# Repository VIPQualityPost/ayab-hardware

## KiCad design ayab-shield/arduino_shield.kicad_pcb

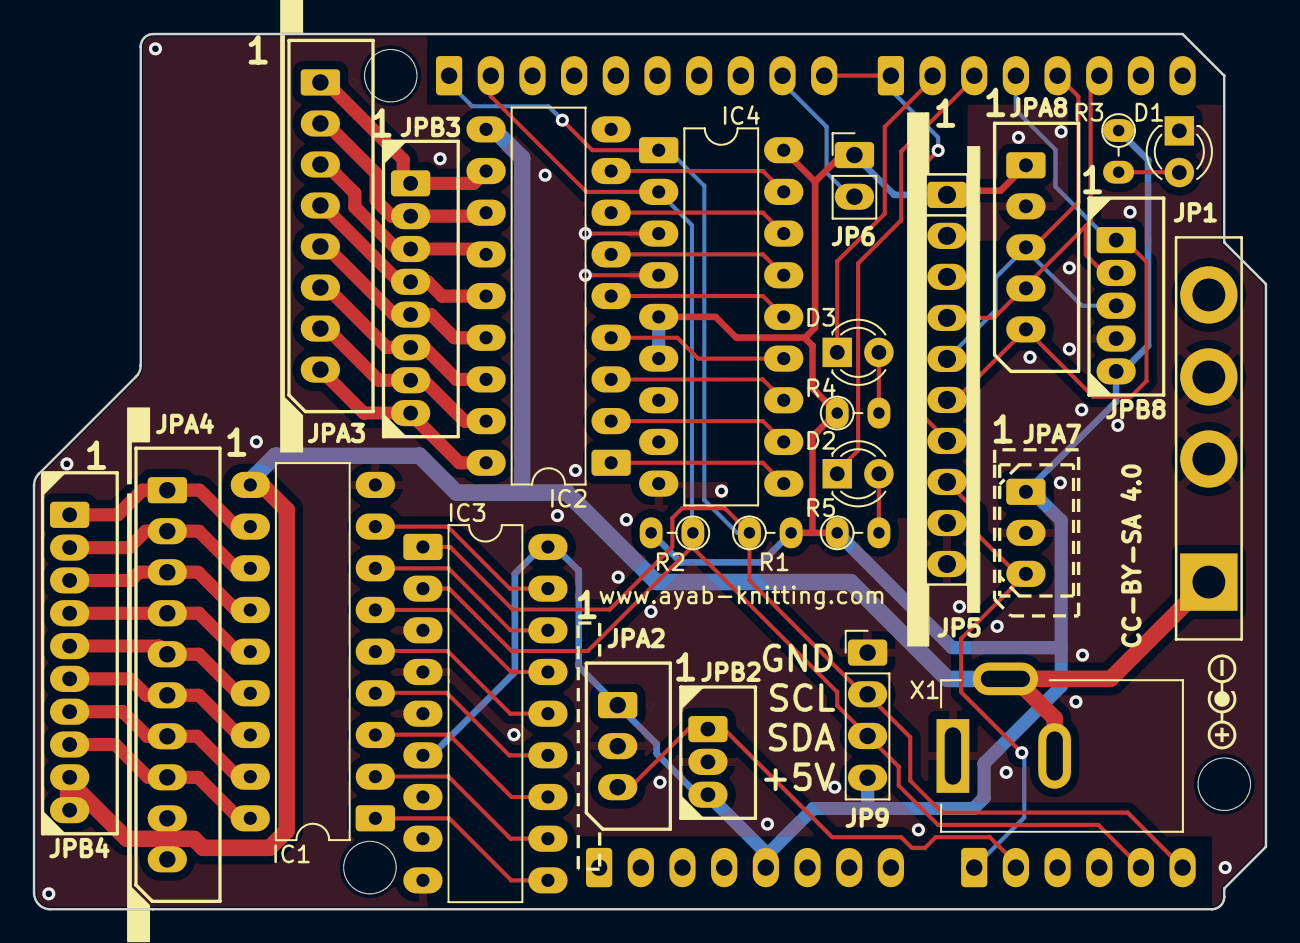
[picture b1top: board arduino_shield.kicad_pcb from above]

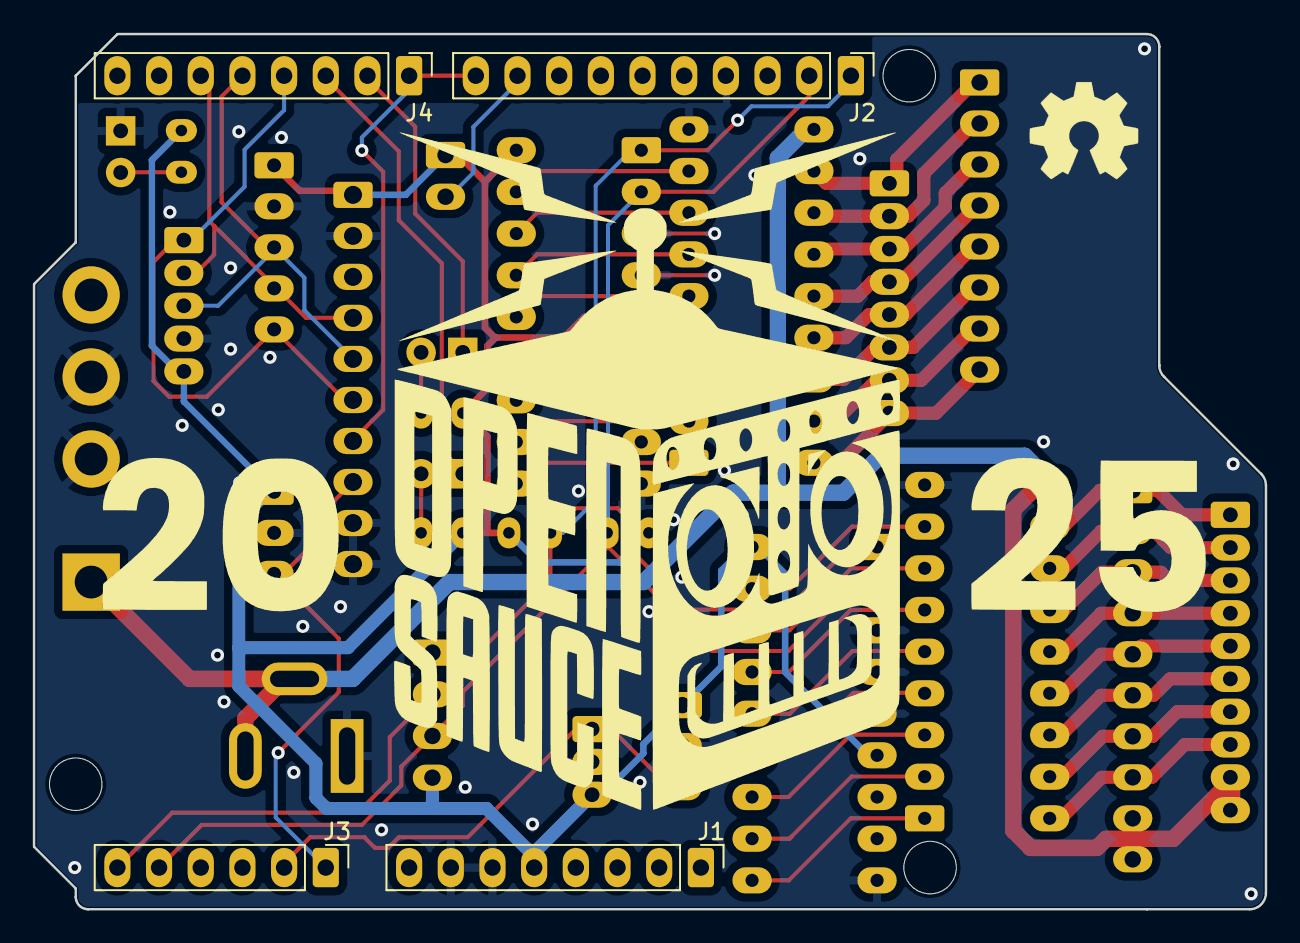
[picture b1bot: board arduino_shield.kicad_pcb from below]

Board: 2 copper layers, 75.1 x 53.3 mm, 34 parts (5 on the bottom side), 49 nets.

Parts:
D1: RED_3MM; LED_D3.0mm
D2: YEL_3MM; LED_D3.0mm
D3: GRN_3MM; LED_D3.0mm
IC1, IC2: ULN2803A; DIP-18_W7.62mm_LongPads
IC3, IC4: MCP2300X/P; DIP-18_W7.62mm_LongPads
J1: Power; PinHeader_1x08_P2.54mm_Vertical_LongPads
J2: Digital/PWM; PinHeader_1x10_P2.54mm_Vertical_LongPads
J3: Analog; PinHeader_1x06_P2.54mm_Vertical_LongPads
J4: Digital/PWM; PinHeader_1x08_P2.54mm_Vertical_LongPads
JP1: BROTHER POWER; Brother_4P
JP5: 1X10 2.5mm; HNC2-2.5P-10DS_LongPads
JP6: 1x2 2.5mm; PinHeader_1x02_P2.54mm_Vertical_LongPads
JP9: 1X5 2.5mm; PinHeader_1x04_P2.54mm_Vertical_LongPads
JPA2: 1X3 2.5mm; Molex_0022035035_or_Hirose_HNC2-2.5P-3DS_LongPads_dashed_bar
JPA3: 1X8 2.5mm; Molex_0022035085_or_Hirose_HNC2_2.5P_8DS_LongPads
JPA4: 1X10 2.5mm; Molex_0022035105_or_Hirose_HNC2-2.5P-10DS_LongPads
JPA7: 1X3 2.5mm; Molex_530140310_or_SPOX_5267-03A_1x03_P2.50mm_Vertical_Long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
JPA8: 1X5 2.5mm; Molex_SPOX_5267-05A_1x05_P2.50mm_Vertical_LongPads
JPB2: 1X3 2mm; 530140310_LongPads
JPB3: 1X8 2mm; 530140810_LongPads
JPB4: 1X10 2mm; 530141010_LongPads
JPB8: 1X5 2mm; 530140510_LongPads
MH1, MH2, MH4: MountingHole_3.2mm
R1, R2: 4K7; R_Axial_DIN0204_L3.6mm_D1.6mm_P2.54mm_Vertical_LongPads
R3, R4, R5: 150; R_Axial_DIN0204_L3.6mm_D1.6mm_P2.54mm_Vertical_LongPads
X1: KLDX-0202-AC; BarrelJack_Kycon_KLDX-0202-xC_Horizontal
kibuzzard-686AF158: G***; kibuzzard-686AF158

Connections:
+5V: IC3.6 (~RESET), IC3.18 (VDD), IC4.5 (A0), IC4.6 (~RESET), IC4.18 (VDD), J1.5, JP5.1, JP6.1, JP9.4, JPA2.1, JPA7.1, JPA8.1, JPB2.3, JPB8.5, R1.2, R2.2, R3.1, R4.1, R5.1
+15V: IC1.10 (COM), IC2.10 (COM), JP1.1 (+15V), JPA4.9, JPA4.10, JPB4.9, JPB4.10, X1.2, X1.3
/910_L: J2.10, J4.1, JP5.7
/BUZZ: J2.9, JP6.2
/ENC_A: J4.6, JP5.4, JPA8.4, JPB8.2
/ENC_B: J4.5, JP5.5, JPA8.3, JPB8.3
/ENC_C: J4.4, JP5.6, JPA8.5, JPB8.1
/EOL_L: J3.2, JPA2.3, JPB2.1
/EOL_R: J3.1, JP5.8, JPA7.3
/LED_GRN: D3.1 (K), J4.2
/LED_YEL: D2.1 (K), J4.3
/SCL: IC3.1 (SCL), IC4.1 (SCL), J2.1, J3.6, JP9.2, R1.1
/SDA: IC3.2 (SDA), IC4.2 (SDA), J2.2, J3.5, JP9.3, R2.1
GND: D1.1 (K), IC1.9 (GND), IC2.9 (GND), IC3.3 (A2), IC3.4 (A1), IC3.5 (A0), IC3.9 (VSS), IC4.3 (A2), IC4.4 (A1), IC4.9 (VSS), J1.6, J1.7, J2.4, JP1.2 (GND), JP1.3 (GND), JP5.2, JP5.9, JP5.10, JP9.1, JPA2.2, JPA7.2, JPA8.2, JPB2.2, JPB8.4, X1.1
unnamed: D1.2 (A), R3.2
unnamed: D2.2 (A), R5.2
unnamed: D3.2 (A), R4.2
unnamed: IC1.1 (I1), IC3.10 (GP0)
unnamed: IC1.2 (I2), IC3.11 (GP1)
unnamed: IC1.3 (I3), IC3.12 (GP2)
unnamed: IC1.4 (I4), IC3.13 (GP3)
unnamed: IC1.5 (I5), IC3.14 (GP4)
unnamed: IC1.6 (I6), IC3.15 (GP5)
unnamed: IC1.7 (I7), IC3.16 (GP6)
unnamed: IC1.8 (I8), IC3.17 (GP7)
unnamed: IC1.18 (O1), JPA4.8, JPB4.8
unnamed: IC1.17 (O2), JPA4.7, JPB4.7
unnamed: IC1.16 (O3), JPA4.6, JPB4.6
unnamed: IC1.15 (O4), JPA4.5, JPB4.5
unnamed: IC1.14 (O5), JPA4.4, JPB4.4
unnamed: IC1.13 (O6), JPA4.3, JPB4.3
unnamed: IC1.12 (O7), JPA4.2, JPB4.2
unnamed: IC1.11 (O8), JPA4.1, JPB4.1
unnamed: IC2.1 (I1), IC4.10 (GP0)
unnamed: IC2.2 (I2), IC4.11 (GP1)
unnamed: IC2.3 (I3), IC4.12 (GP2)
unnamed: IC2.4 (I4), IC4.13 (GP3)
unnamed: IC2.5 (I5), IC4.14 (GP4)
unnamed: IC2.6 (I6), IC4.15 (GP5)
unnamed: IC2.7 (I7), IC4.16 (GP6)
unnamed: IC2.8 (I8), IC4.17 (GP7)
unnamed: IC2.18 (O1), JPA3.8, JPB3.8
unnamed: IC2.17 (O2), JPA3.7, JPB3.7
unnamed: IC2.16 (O3), JPA3.6, JPB3.6
unnamed: IC2.15 (O4), JPA3.5, JPB3.5
unnamed: IC2.14 (O5), JPA3.4, JPB3.4
unnamed: IC2.13 (O6), JPA3.3, JPB3.3
unnamed: IC2.12 (O7), JPA3.2, JPB3.2
unnamed: IC2.11 (O8), JPA3.1, JPB3.1

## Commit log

2025-04-13 Change CI to use JobSets instead of manually constructing all outputs with kicad-cli
2025-04-13 add workflow dispatch to manually run jobs
2025-04-13 typo
2025-04-13 Workflow name clarity
2025-04-13 missing $ on env var
2025-04-13 Fix a few more typos
2025-04-13 fix filepaths
2025-04-13 typo for shield project name
2025-04-13 remove conditional check for merged documentation build
2025-04-13 missing $
2025-04-13 another missing $
2025-04-13 add ghostscript dependency, fix readme name and remove old renders
2025-04-13 Fix ghostscript file naming
2025-04-13 add reference path
2025-04-13 update BOM export script
2025-04-13 update bom formatter
2025-04-13 fix JobSet POS file format + python formatter
2025-04-13 kicad pos naming is driving me nuts
2025-04-13 UGHHH
2025-04-13 Try to fix ordering of committing and generating files
2025-04-13 Oops broke workflow
2025-04-13 broke it.. again
2025-04-13 Wrong git checkout flag
2025-04-13 Missing |
2025-04-13 Try to fix git / gh interop
2025-04-13 Add reference material to repo [skip ci]
2025-04-14 Fix pos file naming
2025-04-14 Remove git junk
2025-04-14 kicad is killing me
2025-04-14 Add upload materials back to repo
2025-04-14 Add design file PDFs to repo [skip ci]
2025-04-14 Add reference materials to repo [skip ci]
2025-04-14 Update arduino_shield.kicad_pro
    Dummy change to check what happens with PRs from forks.
2025-07-06 open sauce special edition
2025-12-16 save in version 9

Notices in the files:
ayab-shield/arduino_shield.kicad_pcb:
CC-BY-SA 4.0
